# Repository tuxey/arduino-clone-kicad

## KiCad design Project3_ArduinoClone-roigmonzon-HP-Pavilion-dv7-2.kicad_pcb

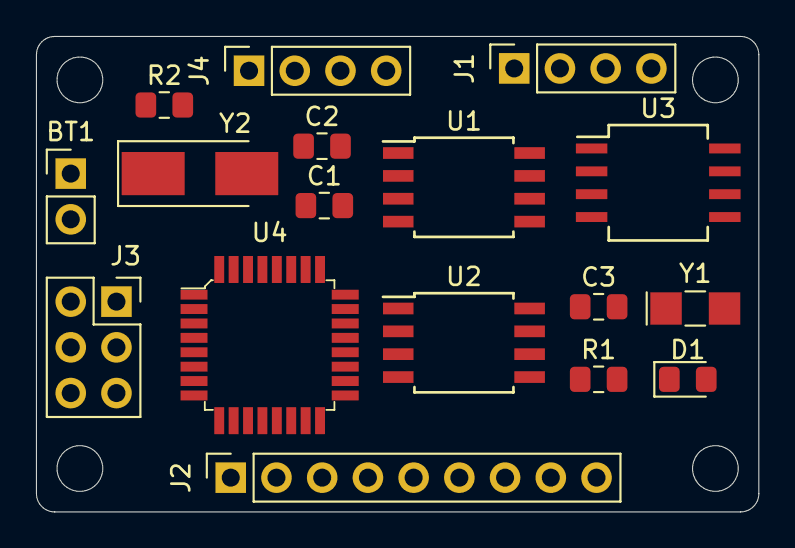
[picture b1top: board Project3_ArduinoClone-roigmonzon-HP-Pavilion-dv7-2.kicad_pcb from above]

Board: 2 copper layers, 40.1 x 26.4 mm, 17 parts (0 on the bottom side), 24 nets, no tracks yet.

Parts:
BT1: Battery 3V; PinHeader_1x02_P2.54mm_Vertical
C1, C2: 22pF; C_0805_2012Metric_Pad1.15x1.40mm_HandSolder
C3: 10uF; C_0805_2012Metric_Pad1.15x1.40mm_HandSolder
D1: LED; LED_0805_2012Metric_Pad1.15x1.40mm_HandSolder
J1: Serial; PinSocket_1x04_P2.54mm_Vertical
J2: Digital pins; PinSocket_1x09_P2.54mm_Vertical
J3: ICSP; PinSocket_2x03_P2.54mm_Vertical
J4: I2C; PinSocket_1x04_P2.54mm_Vertical
R1: 330Ohm; R_0805_2012Metric_Pad1.15x1.40mm_HandSolder
R2: 10kOhm; R_0805_2012Metric_Pad1.15x1.40mm_HandSolder
U1, U2: 24LC1025; SOIJ-8_5.3x5.3mm_P1.27mm
U3: DS1337_v1; SO-8_5.3x6.2mm_P1.27mm
U4: ATMEGA328P-AU; TQFP-32_7x7mm
Y1: Crystal 32 MHz; Crystal_SMD_MicroCrystal_CC7V-T1A-2Pin_3.2x1.5mm_HandSolder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
Y2: Crystal 16 MHz; Crystal_SMD_5032-2Pin_5.0x3.2mm_HandSoldering

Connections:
/ADDS1: U1.1, U2.1, U4.23
/ADDS2: U1.2, U2.2, U4.24
/D2: J2.1, U4.32
/D3: J2.2, U4.1
/D4: J2.3, U4.2
/D5: J2.4, U4.9
/D6: J2.5, U4.10
/D7: J2.6, U4.11
/D8: J2.7, U4.12
/MISO: J3.1, U4.16
/MOSI: J3.4, U4.15
/RESET: J3.5, R2.2, U4.29
/RX: J1.3, U4.30
/SCK: D1.2, J3.3, U4.17
/SCL: J4.4, U1.6, U2.6, U3.6, U4.28
/SDA: J4.3, U1.5, U2.5, U3.5, U4.27
/TX: J1.4, U4.31
/VCC: BT1.1, C3.1, J1.2, J2.9, J3.2, J4.2, R2.1, U1.3, U1.8, U2.3, U2.8, U3.3, U3.8, U4.4, U4.6, U4.18, U4.20
GND: BT1.2, C1.1, C2.1, C3.2, J1.1, J2.8, J3.6, J4.1, R1.2, U1.4, U1.7, U2.4, U2.7, U3.4, U4.3, U4.5, U4.21
unnamed: C1.2, U4.7, Y2.1
unnamed: C2.2, U4.8, Y2.2
unnamed: D1.1, R1.1
unnamed: U3.1, Y1.1
unnamed: U3.2, Y1.2

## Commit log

2019-10-12 Initial commit
    Changes to be committed:
    new file: Project3_ArduinoClone.kicad_pcb
    new file: Project3_ArduinoClone.pro
    new file: Project3_ArduinoClone.sch
2019-10-12 Setup the title block in the schematic sheet
2019-10-12 Changed description line: EEPROM is 512 kB, not 1 kB.
2019-10-13 Added list of parts. Added project symbols, except ATMEGA328. Added child sheet with connectors.
    Changes to be committed:
    new file: Connectors.sch
    new file: Portatil/Project3_ArduinoClone-roigmonzon-HP-Pavilion-dv7.pro
    new file: Portatil/Project3_ArduinoClone-roigmonzon-HP-Pavilion-dv7.sch
    new file: Project 3 parts.txt
    modified: Project3_ArduinoClone-cache.lib
2019-10-13 Added DS1337 schematic symbol (custom created).
2019-10-13 Added missing crystals.
2019-10-13 Annotated.
2019-10-14 Footprints assigned.
    Review with real footprints that I'm going to use.
2019-10-14 Place labels on connectors sheet & wire
2019-10-14 Wire entire root sheet
2019-10-15 Comment sections and generate netlist
2019-10-15 Minor aesthetical schematic changes
2019-10-16 Add sheet info in pcbnew
2019-10-16 Import netlist and create netclasses
2019-10-16 First version of the placement
2019-10-16 Improve placement, create outline
2019-10-16 Autoroute 2 and 4 layer version
    Save different pcbnew files for each version
    Create copper zone in 2 layer version,
    and that is the main pcbnew file.
2019-10-16 Add silkscreen text
2019-10-17 Final silkscreen, generate gerbers
